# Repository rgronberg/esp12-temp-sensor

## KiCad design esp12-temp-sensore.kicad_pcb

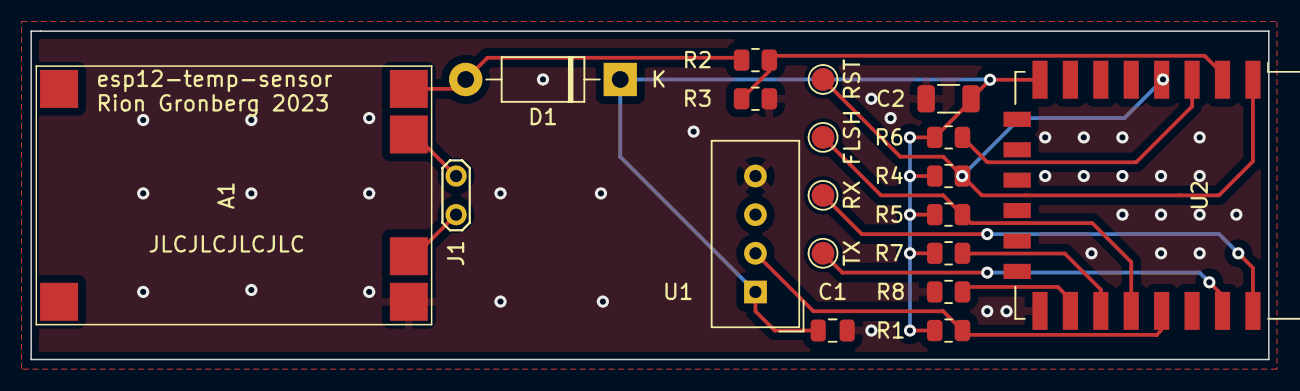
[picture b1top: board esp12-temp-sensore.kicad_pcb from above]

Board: 2 copper layers, 81.4 x 21.6 mm, 20 parts (1 on the bottom side), 14 nets.

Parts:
A1: TP4056; TP4056-mod
BT1: Battery; BatteryHolder_MPD_BH-18650-PC2
C1: 100nF; C_0805_2012Metric
C2: 22uF; C_1206_3216Metric
D1: 1N5817; D_DO-41_SOD81_P10.16mm_Horizontal
J1: TestPoint_2Pole; TestPoint_2Pads_Pitch2.54mm_Drill0.8mm
R1, R4, R5, R6, R7, R8: 10KR; R_0805_2012Metric
R2: 1MR; R_0805_2012Metric
R3: 300KR; R_0805_2012Metric
T1: RST; TestPoint_Pad_D1.5mm
T2: FLSH; TestPoint_Pad_D1.5mm
T3: RX; TestPoint_Pad_D1.5mm
T4: TX; TestPoint_Pad_D1.5mm
U1: DHT11; Aosong_DHT11_5.5x12.0_P2.54mm
U2: ESP-12F; ESP-12E

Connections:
+BATT: A1.3 (B+), J1.1
-BATT: A1.4 (B-), J1.2
/+BATT_PROT: A1.5 (OUT+), D1.2 (A), R2.1
/BATT_LVL: R2.2, R3.1, U2.2 (ADC)
/EN: R6.2, U2.3 (EN)
/FLASH: R5.2, T2.1, U2.18 (GPIO0)
/HI_BOOT: R7.2, U2.17 (GPIO2)
/LOW_BOOT: R8.1, U2.16 (GPIO15)
/RST: R4.2, T1.1, U2.1 (~RST), U2.4 (GPIO16)
/SENSOR: R1.2, U1.2 (IO), U2.19 (GPIO4)
/SERIAL_RX: T3.1, U2.22 (GPIO1/TXD)
/SERIAL_TX: T4.1, U2.21 (GPIO3/RXD)
GND: A1.6 (OUT-), C1.2, C2.1, R3.2, R8.2, U1.4 (GND), U2.15 (GND)
VDC: C1.1, C2.2, D1.1 (K), R1.1, R4.1, R5.1, R6.1, R7.1, U1.1 (VCC), U2.8 (VCC)
